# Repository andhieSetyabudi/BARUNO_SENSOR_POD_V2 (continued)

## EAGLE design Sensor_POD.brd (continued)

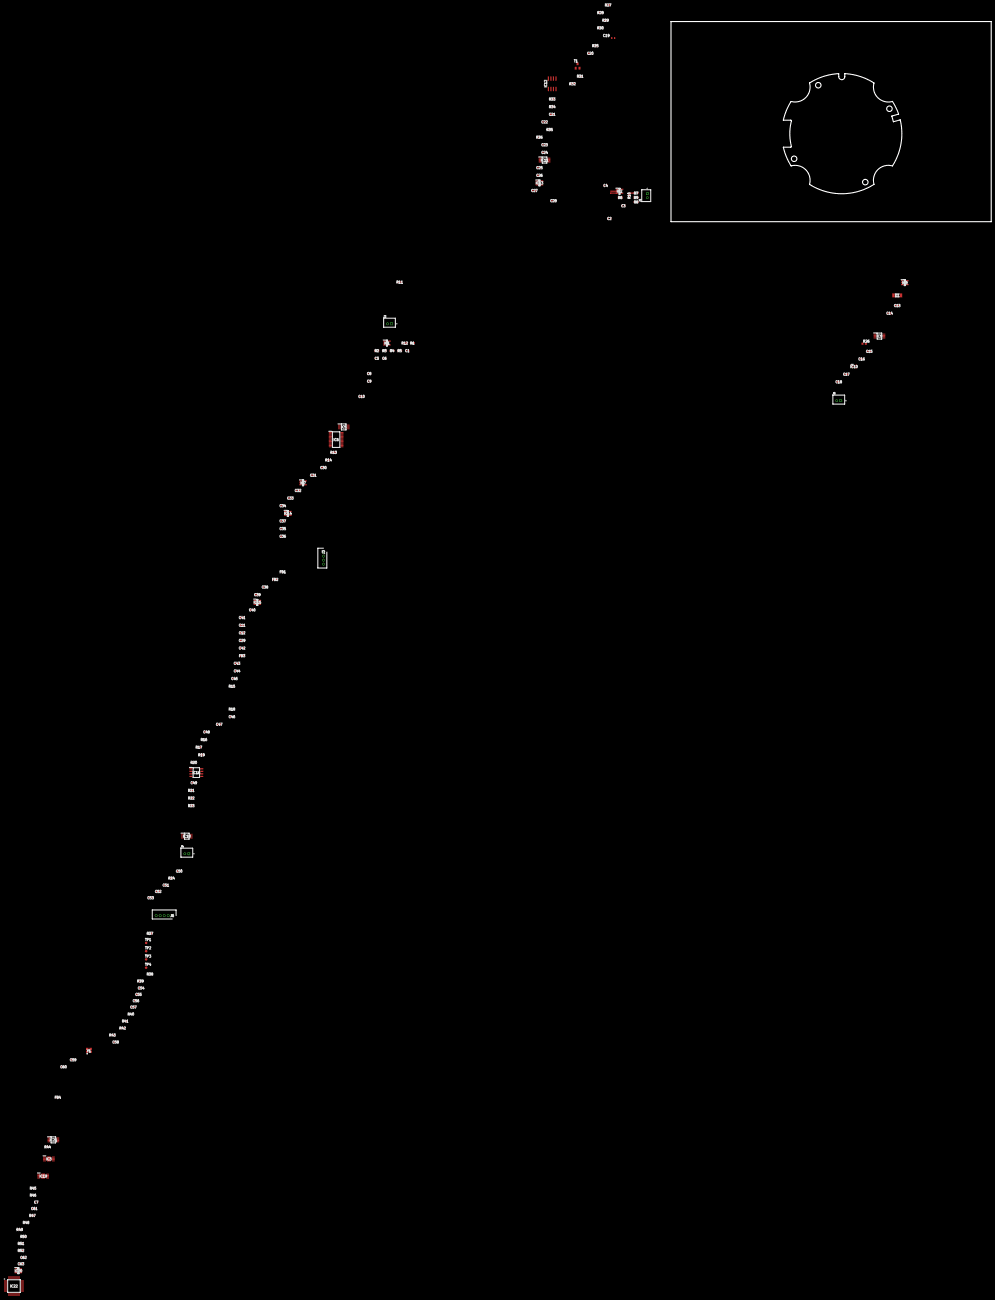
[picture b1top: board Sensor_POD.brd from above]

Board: 2 copper layers, 160.0 x 100.0 mm, 152 parts (0 on the bottom side), 99 nets.
